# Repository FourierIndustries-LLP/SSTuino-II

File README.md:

Designed by FourierIndustries LLP | Designed and tested in Singapore

# SSTuino II

SSTuino II is an easy to use and industrial-ready Wi-Fi enabled microcontroller, designed and fabricated by SST Alumni. With a smaller form factor, improved Wi-Fi and processing capabilities, this is the next generation of SSTuino.

**SSTuino II documentation available at: https://knowledge.fourier.industries**

## Technical information

### Pinout diagram

### Repository Layout

* **SSTuino_II**: CAD files for SSTuino II
* **SSTuinoII_Jig**: CAD files for the SSTuino II test jig
* **Manufacturing**: Manufacturing files (Gerbers, BOM, component placement)
* **Documentation**: Documentation for design and manufacturing (not user manuals)
* **Tooling**: Software tools for production and debugging of the SSTuino II

### Automatic repair tool

Paste and run the following command in your terminal to run the autorepair tool, should you run into difficulty launching Arduino IDE or uploading programs onto your SSTuino II. Follow the on-screen instructions carefully. 

Note: This tool is only compatible with Arduino IDE 2. 

```shell
/bin/bash -c "$(curl -fsSL https://raw.githubusercontent.com/FourierIndustries-LLP/SSTuino-II/HEAD/Tooling/sstuino-autorepair.sh)"
```

## Contributing

Contributing to the SSTuino II Git Repository requires you to have EAGLE 8.4 or newer which supports Managed Libraries.

SSTuino II primarily uses EAGLE's Managed Libraries made by Sparkfun, but also contain our own custom footprints and SMD component footprints from various manufacturers.

SSTuino II is derived from the [Arduino Uno WiFi REV2](https://store-usa.arduino.cc/products/arduino-uno-wifi-rev2), and is licensed under a [CC BY-SA 4.0 International license](http://creativecommons.org/licenses/by-sa/4.0/).

## Our team

* Goh Qian Zhe ([@QianZheGoh](https://twitter.com/QianZheGoh))
* Pan Ziyue ([@d3lta-v](https://twitter.com/sammy0025))

And special acknowledgement to the awesome folks at Arduino, Sparkfun and Adafruit for technical reference and ECAD models.

Open Source Hardware (OSHW)

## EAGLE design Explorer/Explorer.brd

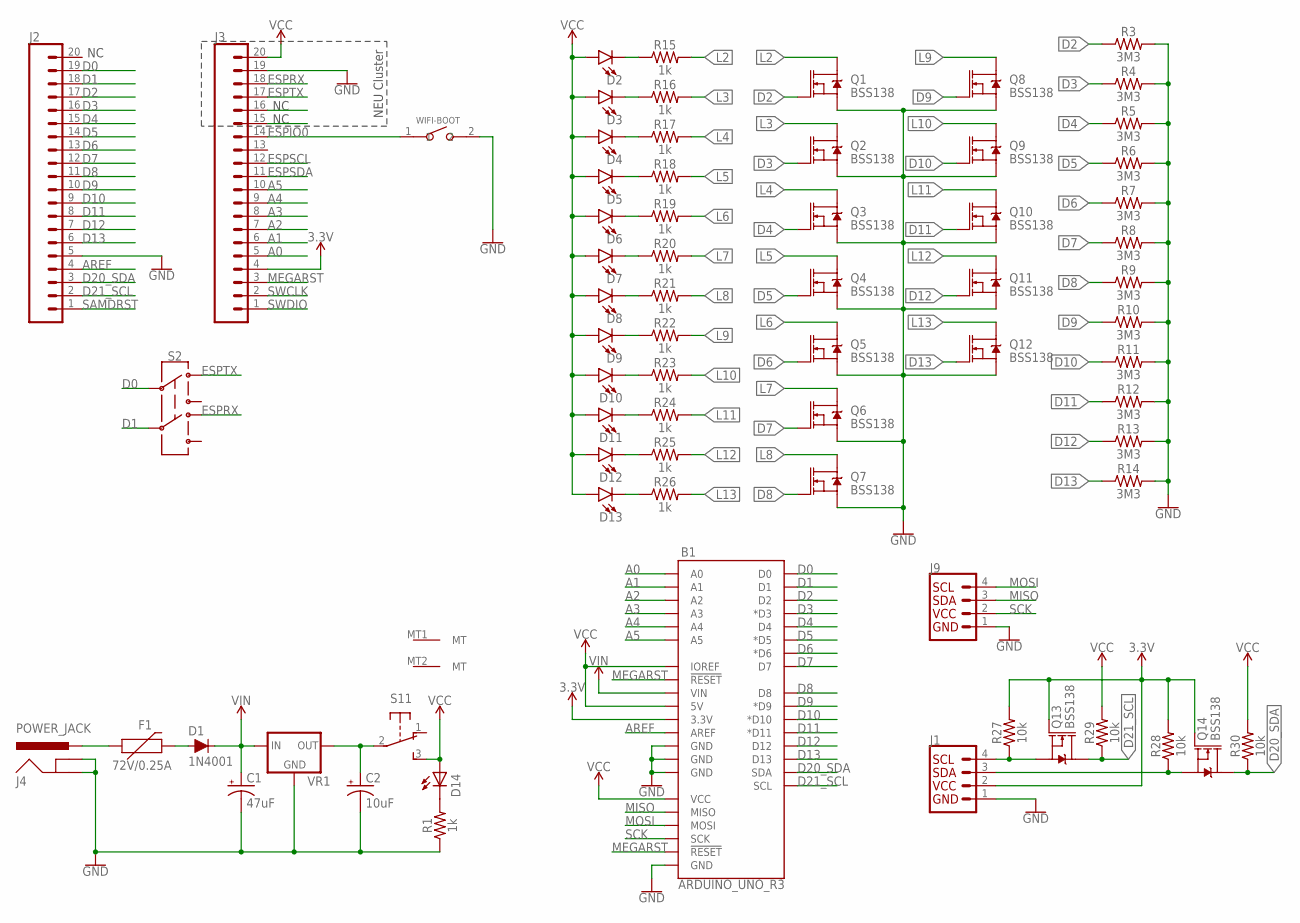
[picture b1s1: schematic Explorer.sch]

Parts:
B1: ARDUINO_UNO_R3; ARDUINO_R3
C1: 47uF; CPOL-RADIAL-2.5MM-6.5MM
C2: 10uF; CPOL-RADIAL-2.5MM-6.5MM
D1: 1N4001; DIODE-1N4001-KIT
D2, D3, D4, D5, D6, D7, D8, D9, D10, D11, D12, D13: LED0603; LED-0603; LCSC_PART C2286
D14: LEDCHIPLED_0805; CHIPLED_0805; LCSC_PART C2296
F1: 72V/0.25A; PTH
J1, J9: QWIIC_CONNECTORJS-1MM; 1X04_1MM_RA; LCSC_PART C239522
J2, J3: CONN_20; 1X20; LCSC_PART C50984
J4: POWER_JACK; POWER_JACK_PTH
Q1, Q2, Q3, Q4, Q5, Q6, Q7, Q8, Q9, Q10, Q11, Q12, Q13, Q14: BSS138; SOT23-3; LCSC_PART C435876
R1, R15, R16, R17, R18, R19, R20, R21, R22, R23, R24, R25, R26: 1k; 0603; LCSC_PART C21190
R3, R4, R5, R6, R7, R8, R9, R10, R11, R12, R13, R14: 3M3; 0603; LCSC_PART C103556
R27, R28, R29, R30: 10k; 0603; LCSC_PART C25804
S1: EG1213
S2: SWITCH-DPDT-SMD-AYZ0202; SWITCH_DPDT_SMD_AYZ0202; LCSC_PART C318999
VR1: V_REG_78XXSINK; TO220-IGO
WIFI-BOOT: SKRKAEE020; SW2-2.6-3.9X2.9X1.5+0.4MM; LCSC_PART C455280

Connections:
3.3V: B1.3.3V, J1.2 (VCC), J3.4, Q13.1 (G), Q14.1 (G), R27.2, R28.2
A0: B1.A0, J3.5
A1: B1.A1, J3.6
A2: B1.A2, J3.7
A3: B1.A3, J3.8
A4: B1.A4, J3.9
A5: B1.A5, J3.10
AREF: B1.AREF, J2.4
D0: B1.D0, J2.19, S2.2
D1: B1.D1, J2.18, S2.5
D2: B1.D2, J2.17, Q1.1 (G), R3.1
D3: B1.D3 (*D3), J2.16, Q2.1 (G), R4.1
D4: B1.D4, J2.15, Q3.1 (G), R5.1
D5: B1.D5 (*D5), J2.14, Q4.1 (G), R6.1
D6: B1.D6 (*D6), J2.13, Q5.1 (G), R7.1
D7: B1.D7, J2.12, Q6.1 (G), R8.1
D8: B1.D8, J2.11, Q7.1 (G), R9.1
D9: B1.D9 (*D9), J2.10, Q8.1 (G), R10.1
D10: B1.D10 (*D10), J2.9, Q9.1 (G), R11.1
D11: B1.D11 (*D11), J2.8, Q10.1 (G), R12.1
D12: B1.D12, J2.7, Q11.1 (G), R13.1
D13: B1.D13, J2.6, Q12.1 (G), R14.1
D20_SDA: B1.SDA, J2.3, Q14.3 (D), R30.1
D21_SCL: B1.SCL, J2.2, Q13.3 (D), R29.1
ESPIO0: J3.14, WIFI-BOOT.1
ESPRX: J3.18, S2.4
ESPSCL: J3.12
ESPSDA: J3.11
ESPTX: J3.17, S2.1
GND: B1.GND@1 (GND), B1.GND@2 (GND), B1.GND@3 (GND), B1.GND@4 (GND), C1.2 (-), C2.2 (-), J1.1 (GND), J2.5, J3.19, J4.GND, J4.GNDBREAK, J9.1 (GND), Q1.2 (S), Q2.2 (S), Q3.2 (S), Q4.2 (S), Q5.2 (S), Q6.2 (S), Q7.2 (S), Q8.2 (S), Q9.2 (S), Q10.2 (S), Q11.2 (S), Q12.2 (S), R1.1, R3.2, R4.2, R5.2, R6.2, R7.2, R8.2, R9.2, R10.2, R11.2, R12.2, R13.2, R14.2, VR1.GND, WIFI-BOOT.2
L2: Q1.3 (D), R15.2
L3: Q2.3 (D), R16.2
L4: Q3.3 (D), R17.2
L5: Q4.3 (D), R18.2
L6: Q5.3 (D), R19.2
L7: Q6.3 (D), R20.2
L8: Q7.3 (D), R21.2
L9: Q8.3 (D), R22.2
L10: Q9.3 (D), R23.2
L11: Q10.3 (D), R24.2
L12: Q11.3 (D), R25.2
L13: Q12.3 (D), R26.2
MEGARST: B1.RESET@1 (!RESET!), B1.RESET@2 (!RESET!), J3.3
MISO: B1.MISO, J9.3 (SDA)
MOSI: B1.MOSI, J9.4 (SCL)
unnamed: F1.P$1 (1), J4.PWR
unnamed: D1.A, F1.P$2 (2)
unnamed: D14.C, R1.2
unnamed: C2.1 (+), S1.2, VR1.OUT
unnamed: D13.C, R26.1
unnamed: D12.C, R25.1
unnamed: D11.C, R24.1
unnamed: D10.C, R23.1
unnamed: D9.C, R22.1
unnamed: D8.C, R21.1
unnamed: D7.C, R20.1
unnamed: D6.C, R19.1
unnamed: D5.C, R18.1
unnamed: D4.C, R17.1
unnamed: D3.C, R16.1
unnamed: D2.C, R15.1
SAMDRST: J2.1
SCK: B1.SCK, J9.2 (VCC)
SCL_3V: J1.4 (SCL), Q13.2 (S), R27.1
SDA_3V: J1.3 (SDA), Q14.2 (S), R28.1
SWCLK: J3.2
SWDIO: J3.1
VCC: B1.5V, B1.IOREF, B1.VCC, D2.A, D3.A, D4.A, D5.A, D6.A, D7.A, D8.A, D9.A, D10.A, D11.A, D12.A, D13.A, D14.A, J3.20, R29.2, R30.2, S1.3 (S)
VIN: B1.VIN, C1.1 (+), D1.C, VR1.IN

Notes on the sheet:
NEU Cluster

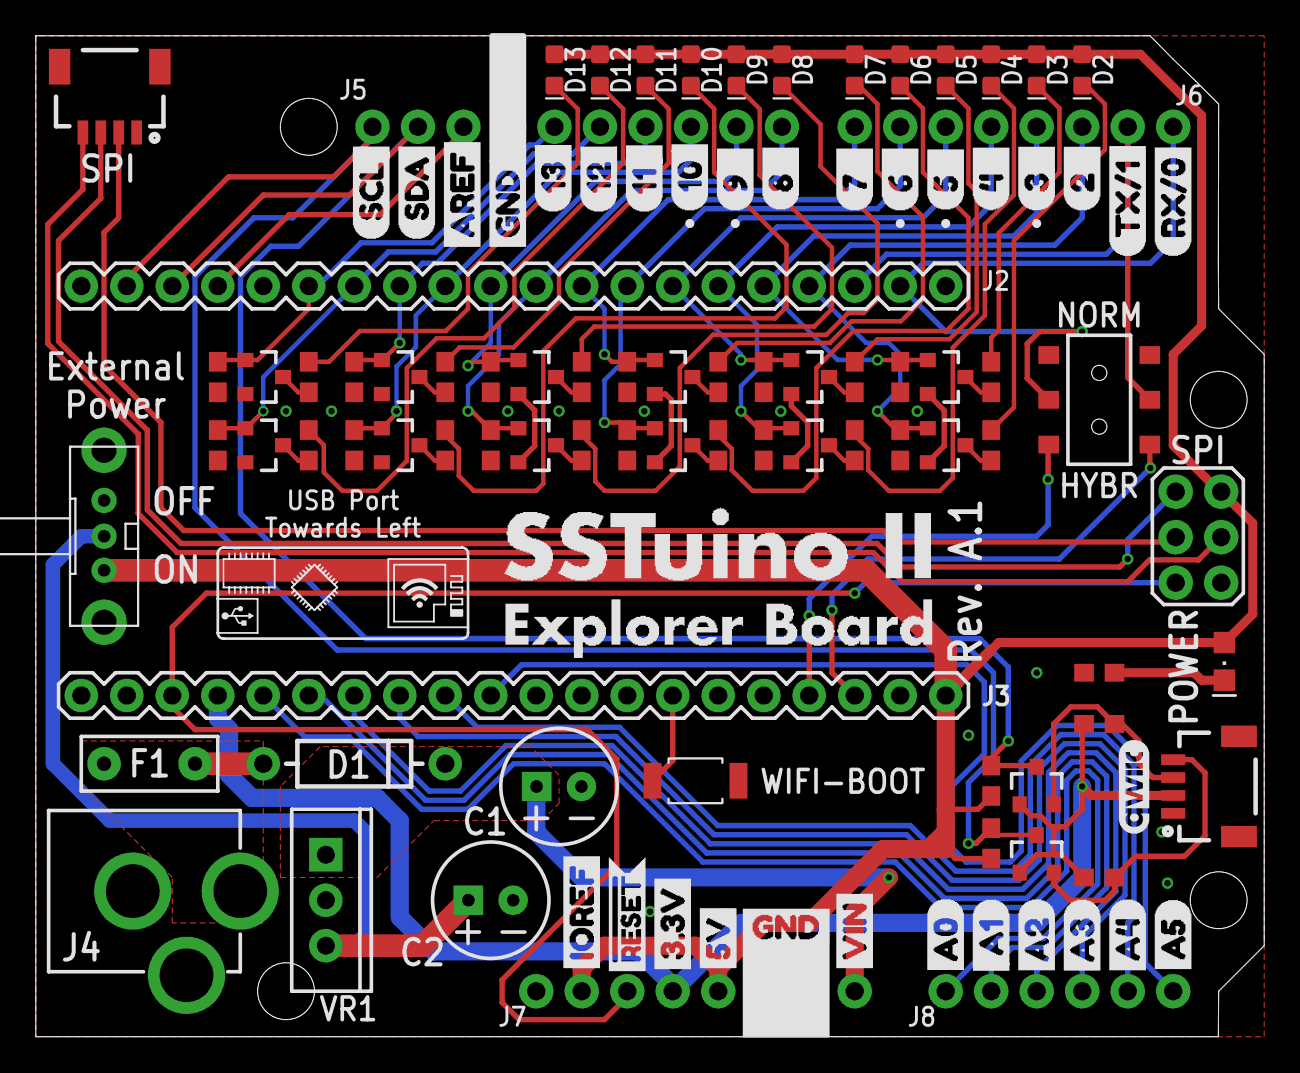
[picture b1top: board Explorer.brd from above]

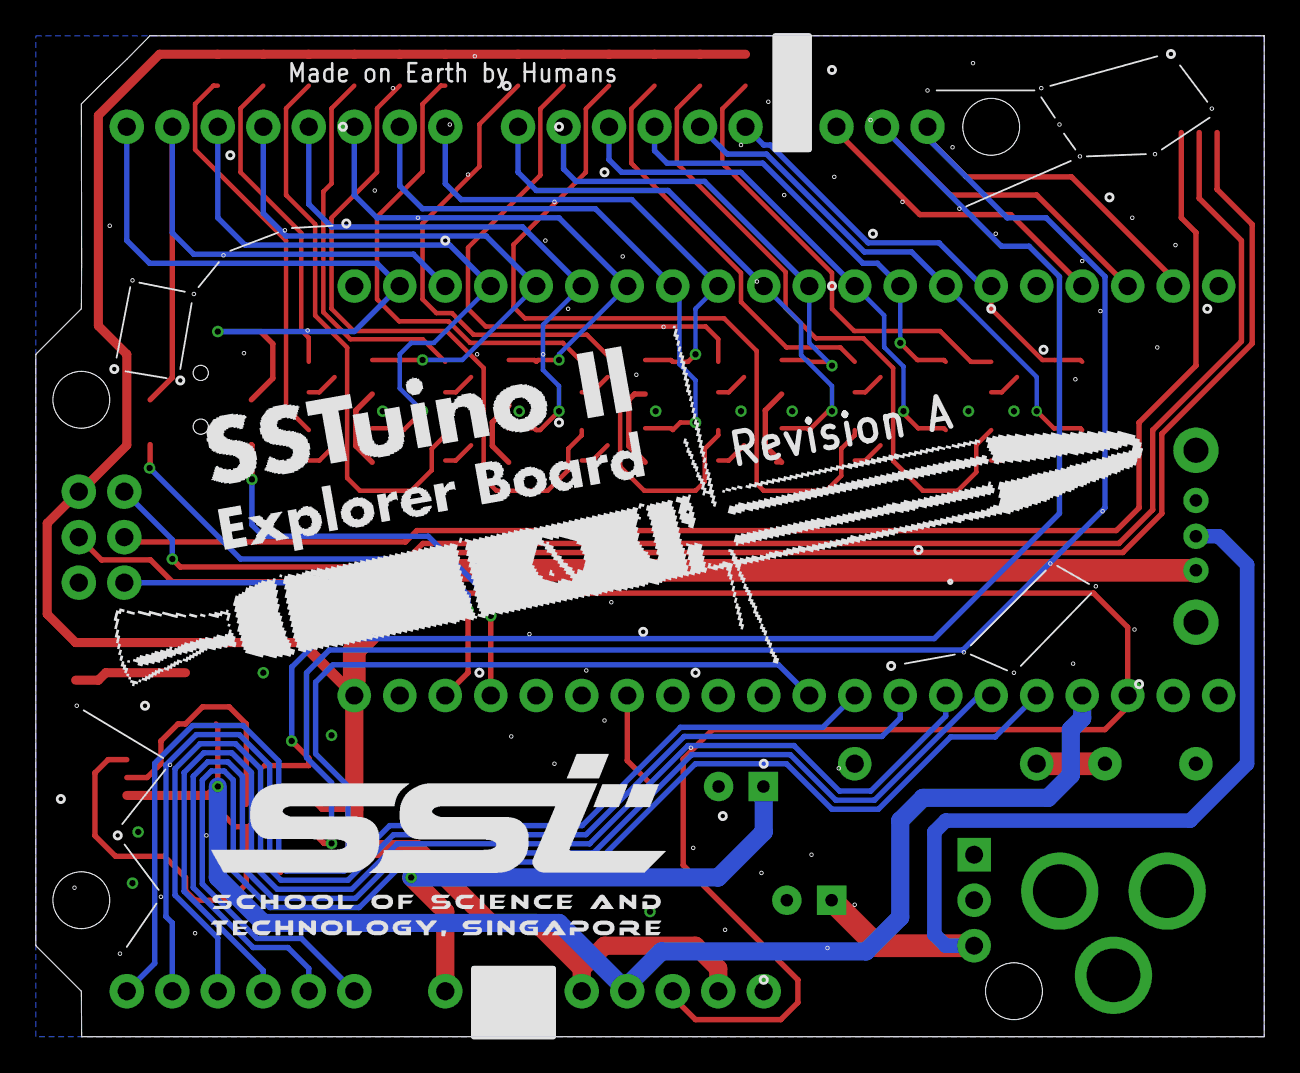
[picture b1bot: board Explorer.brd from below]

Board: 2 copper layers, 68.6 x 55.9 mm, 117 parts (13 on the bottom side), 64 nets.

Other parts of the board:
U$1: IOREF9
U$2: 3#3V7
U$3: #RESET28
U$4: 5V8
U$5, U$25: GND6
U$6: A00
U$7: A11
U$8: SST-BIG
U$9: EXPLORER
U$10: STARFIELD_URSAMINOR
U$11: STARFIELD_SMALL
U$12: STARFIELD_ORION
U$13: STARFIELD_LYRA
U$14: STARFIELD_CASSIOPEIA
U$15, U$16, U$17, U$18, U$19: STARFIELD_SMALL2
U$20: A22
U$21, U$45: EXPLORER_BOARD_LARGE
U$22: A33
U$23: A44
U$24: A55
U$26: 1314
U$27: 1215
U$28: 1116
U$29: 1017
U$30: 9__18
U$31: 8__19
U$32: 7__20
U$33: 6__21
U$34: 5__22
U$35: 4__23
U$36: 3__24
U$37: 2__25
U$38: TX#127
U$39: RX#026
U$40: AREF13
U$41: SDA25
U$42: SCL26
U$43: VIN10
U$44: QWIIC_LOGO
U$46: USBLOGO#PNG
U$47: WIFILOGO#JPG

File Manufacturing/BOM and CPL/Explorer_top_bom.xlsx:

Comment | Designator | Footprint | LCSC Part #
 | D2 D3 D4 D5 D6 D7 D8 D9 D10 D11 D12 D13 | LED-0603 | C2286
 | D14 | LED-0805 | C2296
 | J1 J9 | 1X04_1MM_JST_SH | C145956
 | J2 J3 | 1X20P_FEMALE | C50984
 | S2 | SWITCH_DPDT_SMD_AYZ0202 | C318999
1k | R1 R15 R16 R17 R18 R19 R20 R21 R22 R23 R24 R25 R26 | RES-0603 | C21190
3M3 | R3 R4 R5 R6 R7 R8 R9 R10 R11 R12 R13 R14 | RES-0603 | C39227
10k | R27 R28 R29 R30 | RES-0603 | C25804
BSS138 | Q1 Q2 Q3 Q4 Q5 Q6 Q7 Q8 Q9 Q10 Q11 Q12 Q13 Q14 | SOT23-3 | C435876
SKRKAEE020 | WIFI-BOOT WIFI-RESET | SW2-2.6-3.9X2.9X1.5+0.4MM | C455280
 | J5 | 1X10P_FEMALE | C35445
 | J6 J7 | 1X8P_FEMALE | C27438
 | J8 | 1X6P_FEMALE | C40877
0 | R2 R31 | RES-0603 | C21189

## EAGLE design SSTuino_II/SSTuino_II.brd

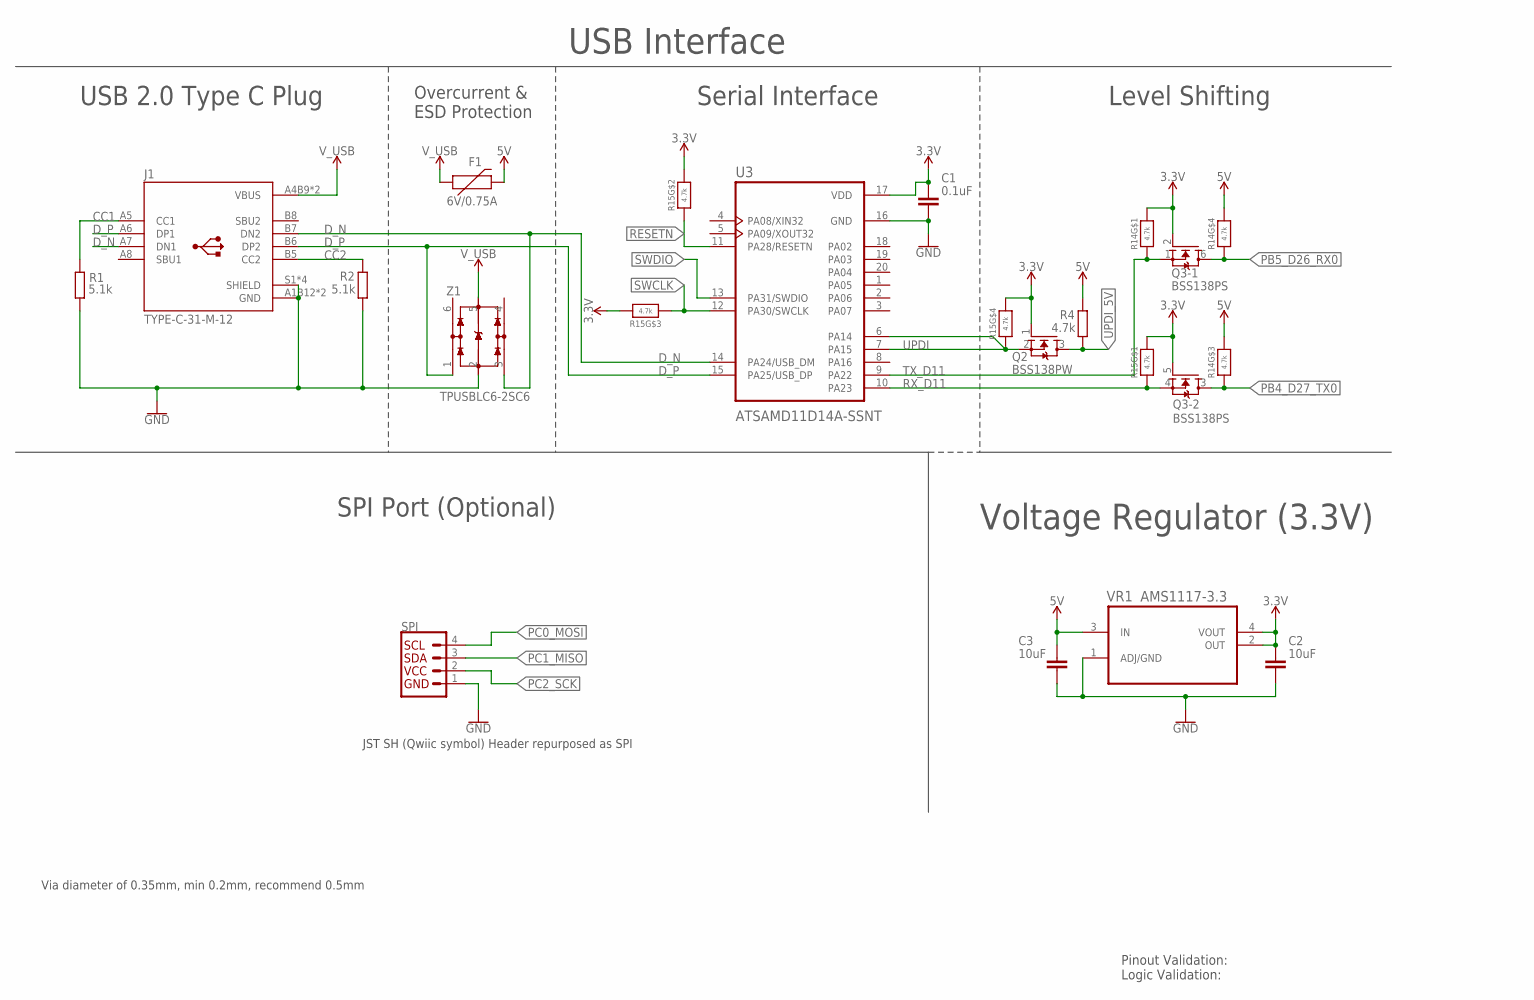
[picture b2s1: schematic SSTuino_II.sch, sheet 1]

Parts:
C1: 0.1uF; CAPC1005X60; LCSC_PART C696352
C2, C3: 10uF; CAPC1608X85; LCSC_PART C19702
F1: 6V/0.75A; 1206; LCSC_PART C99563
J1: TYPE-C-31-M-12; HRO_TYPE-C-31-M-12; LCSC_PART C165948
Q2: BSS138PW; SOT65P210X110-3N; LCSC_PART C193366
Q3: BSS138PS; ARDUINO-TRANSISTORS_SOT363; LCSC_PART C193381
R1, R2: 5.1k; RESC1005X40; LCSC_PART C25905
R4: 4.7k; RESC1005X40; LCSC_PART C25900
R14, R15: 4.7k; RESPACK_4X0402; LCSC_PART C29586
SPI: QWIIC_CONNECTORJS-1MM; 1X04_1MM_RA
U3: ATSAMD11D14A-SSNT; SOIC127P1030X265-20N; LCSC_PART C2053599
VR1: AMS1117-3.3; SOT230P696X180-4N; LCSC_PART C6186
Z1: TPUSBLC6-2SC6; SOT95P280X110-6N; LCSC_PART C558442

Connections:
3.3V: C1.1, C2.1, Q2.1 (G), Q3.2 (G), Q3.5 (G), R14.8 (2), R15.5 (2), R15.6 (2), R15.7 (2), R15.8 (2), U3.17 (VDD), VR1.2 (OUT), VR1.4 (VOUT); also elsewhere on the board
5V: C3.1, F1.2, R4.2, R14.5 (2), R14.6 (2), VR1.3 (IN); also elsewhere on the board
CC1: J1.A5 (CC1), R1.1
CC2: J1.B5 (CC2), R2.2
D_N: J1.A7 (DN1), J1.B7 (DN2), U3.14 (PA24/USB_DM), Z1.3 (IO2)
D_P: J1.A6 (DP1), J1.B6 (DP2), U3.15 (PA25/USB_DP), Z1.1 (IO1)
GND: C1.2, C2.2, C3.2, J1.A1B12 (GND), J1.B1A12 (GND), J1.S1 (SHIELD), J1.S2 (SHIELD), J1.S3 (SHIELD), J1.S4 (SHIELD), R1.2, R2.1, SPI.1 (GND), U3.16 (GND), VR1.1 (ADJ/GND), Z1.2 (VSS); also elsewhere on the board
PB4_D27_TX0: Q3.3 (D), R14.3 (1); also elsewhere on the board
PB5_D26_RX0: Q3.6 (D), R14.4 (1); also elsewhere on the board
PC0_MOSI: SPI.4 (SCL); also elsewhere on the board
PC1_MISO: SPI.3 (SDA); also elsewhere on the board
PC2_SCK: SPI.2 (VCC); also elsewhere on the board
RESETN: R15.2 (1), U3.11 (PA28/RESETN); also elsewhere on the board
RX_D11: Q3.4 (S), R15.1, U3.10 (PA23)
SWCLK: R15.3 (1), U3.12 (PA30/SWCLK); also elsewhere on the board
SWDIO: U3.13 (PA31/SWDIO); also elsewhere on the board
TX_D11: Q3.1 (S), R14.1, U3.9 (PA22)
UPDI: Q2.2 (S), R15.4 (1), U3.6 (PA14), U3.7 (PA15)
UPDI_5V: Q2.3 (D), R4.1; also elsewhere on the board
V_USB: F1.1, J1.A4B9 (VBUS), J1.B4A9 (VBUS), Z1.5 (VCC)

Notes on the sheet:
Via diameter of 0.35mm, min 0.2mm, recommend 0.5mm
USB Interface
Voltage Regulator (3.3V)
USB 2.0 Type C Plug
Overcurrent & ESD Protection
Serial Interface
Level Shifting
Pinout Validation: Logic Validation:
JST SH (Qwiic symbol) Header repurposed as SPI
SPI Port (Optional)

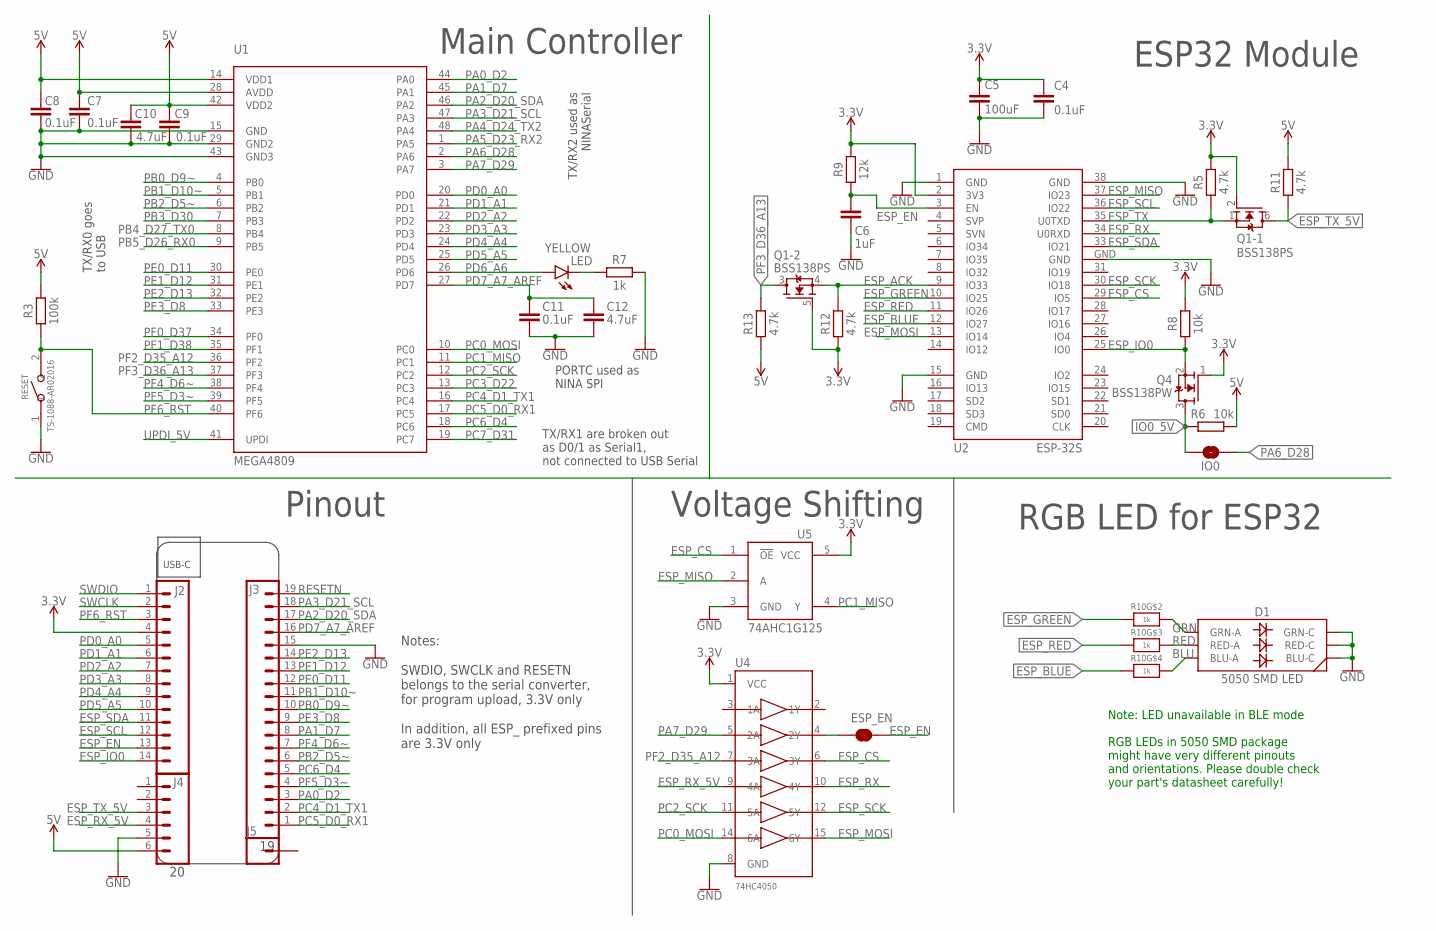
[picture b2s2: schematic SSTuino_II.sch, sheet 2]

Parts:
C4, C11: 0.1uF; CAPC1005X60; LCSC_PART C1525
C5: 100uF; CAPC3216X135; LCSC_PART C15008
C6: 1uF; CAPC1005X60; LCSC_PART C52923
C7, C8, C9: 0.1uF; CAPC1005X60
C10: 4.7uF; CAPC1005X60
C12: 4.7uF; CAPC1005X60; LCSC_PART C23733
D1: 5050 SMD LED; LED-TRICOLOR-5050; LCSC_PART C784540
ESP_EN: JUMPER-SMT_2_NC_TRACE_SILK; SMT-JUMPER_2_NC_TRACE_SILK
IO0: JUMPER-SMT_2_NO_SILK; SMT-JUMPER_2_NO_SILK
J2: CONN_14NO_SILK; 1X14_NO_SILK
J3: CONN_191X19_NO_SILK; 1X19_NO_SILK
J4: CONN_06NO_SILK_FEMALE_PTH; 1X06_NO_SILK
J5: CONN_01PTH_NO_SILK_YES_STOP; 1X01_NO_SILK
LED: YELLOW; LED-0603; LCSC_PART C72038
Q1: BSS138PS; ARDUINO-TRANSISTORS_SOT363; LCSC_PART C193381
Q4: BSS138PW; SOT65P210X110-3N; LCSC_PART C919583
R3: 100k; RESC1005X40; LCSC_PART C25741
R5, R11, R12, R13: 4.7k; RESC1005X40; LCSC_PART C25900
R6, R8: 10k; RESC1005X40; LCSC_PART C25744
R7: 1k; RESC1005X40; LCSC_PART C11702
R9: 12k; RESC1005X40; LCSC_PART C25752
R10: 1k; RESPACK_4X0402; LCSC_PART C25726
RESET: TS-1088-AR02016; SW2-2.6-3.9X2.9X1.5+0.4MM; LCSC_PART C720477
U1: MEGA4809; TQFP48; LCSC_PART C189475
U2: ESP-32S; LCSC_PART C277944
U4: 74HC4050; TSSOP16; LCSC_PART C352825
U5: 74AHC1G125; SOT23-5L; LCSC_PART C7468

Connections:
3.3V: C4.1, C5.1, J2.4, Q1.2 (G), Q1.5 (G), Q4.1 (G), R5.2, R8.2, R9.2, R12.1, U2.2 (3V3), U4.1 (VCC), U5.5 (VCC); also elsewhere on the board
5V: C7.1, C8.1, C9.1, C10.1, J4.6, R3.2, R6.1, R11.2, R13.1, U1.14 (VDD1), U1.28 (AVDD), U1.42 (VDD2); also elsewhere on the board
BLU: D1.6 (BLU-A), R10.5 (2)
ESP_ACK: Q1.4 (S), R12.2, U2.9 (IO33)
ESP_BLUE: R10.4 (1), U2.12 (IO27)
ESP_CS: U2.29 (IO5), U4.6 (3Y), U5.1 (!OE)
ESP_EN: C6.2, ESP_EN.2, J2.13, R9.1, U2.3 (EN)
ESP_EN_PRE: ESP_EN.1, U4.4 (2Y)
ESP_GREEN: R10.2 (1), U2.10 (IO25)
ESP_IO0: J2.14, Q4.2 (S), R8.1, U2.25 (IO0)
ESP_MISO: U2.37 (IO23), U5.2 (A)
ESP_MOSI: U2.13 (IO14), U4.15 (6Y)
ESP_RED: R10.3 (1), U2.11 (IO26)
ESP_RX: U2.34 (U0RXD), U4.10 (4Y)
ESP_RX_5V: J4.4, U4.9 (4A)
ESP_SCK: U2.30 (IO18), U4.12 (5Y)
ESP_SCL: J2.12, U2.36 (IO22)
ESP_SDA: J2.11, U2.33 (IO21)
ESP_TX: Q1.1 (S), R5.1, U2.35 (U0TXD)
ESP_TX_5V: J4.3, Q1.6 (D), R11.1
GND: C4.2, C5.2, C6.1, C7.2, C8.2, C9.2, C10.2, C11.2, C12.2, D1.1 (BLU-C), D1.2 (RED-C), D1.3 (GRN-C), J3.15, J4.5, R7.2, RESET.1, U1.15 (GND), U1.29 (GND2), U1.43 (GND3), U2.1 (GND), U2.15 (GND), U2.38 (GND), U2.GND, U4.8 (GND), U5.3 (GND); also elsewhere on the board
GRN: D1.4 (GRN-A), R10.7 (2)
IO0_5V: IO0.2, Q4.3 (D), R6.2
unnamed: LED.C, R7.1
PA0_D2: J3.3, U1.44 (PA0)
PA1_D7: J3.8, U1.45 (PA1)
PA2_D20_SDA: J3.17, U1.46 (PA2)
PA3_D21_SCL: J3.18, U1.47 (PA3)
PA4_D24_TX2: U1.48 (PA4)
PA5_D23_RX2: U1.1 (PA5)
PA6_D28: IO0.1, U1.2 (PA6)
PA7_D29: U1.3 (PA7), U4.5 (2A)
PB0_D9~: J3.10, U1.4 (PB0)
PB1_D10~: J3.11, U1.5 (PB1)
PB2_D5~: J3.6, U1.6 (PB2)
PB3_D30: U1.7 (PB3)
PB4_D27_TX0: U1.8 (PB4); also elsewhere on the board
PB5_D26_RX0: U1.9 (PB5); also elsewhere on the board
PC0_MOSI: U1.10 (PC0), U4.14 (6A); also elsewhere on the board
PC1_MISO: U1.11 (PC1), U5.4 (Y); also elsewhere on the board
PC2_SCK: U1.12 (PC2), U4.11 (5A); also elsewhere on the board
PC3_D22: U1.13 (PC3)
PC4_D1_TX1: J3.2, U1.16 (PC4)
PC5_D0_RX1: J3.1, U1.17 (PC5)
PC6_D4: J3.5, U1.18 (PC6)
PC7_D31: U1.19 (PC7)
PD0_A0: J2.5, U1.20 (PD0)
PD1_A1: J2.6, U1.21 (PD1)
PD2_A2: J2.7, U1.22 (PD2)
PD3_A3: J2.8, U1.23 (PD3)
PD4_A4: J2.9, U1.24 (PD4)
PD5_A5: J2.10, U1.25 (PD5)
PD6_A6: LED.A, U1.26 (PD6)
PD7_A7_AREF: C11.1, C12.1, J3.16, U1.27 (PD7)
PE0_D11: J3.12, U1.30 (PE0)
PE1_D12: J3.13, U1.31 (PE1)
PE2_D13: J3.14, U1.32 (PE2)
PE3_D8: J3.9, U1.33 (PE3)
PF0_D37: U1.34 (PF0)
PF1_D38: U1.35 (PF1)
PF2_D35_A12: U1.36 (PF2), U4.7 (3A)
PF3_D36_A13: Q1.3 (D), R13.2, U1.37 (PF3)
PF4_D6~: J3.7, U1.38 (PF4)
PF5_D3~: J3.4, U1.39 (PF5)
PF6_RST: J2.3, R3.1, RESET.2, U1.40 (PF6)
RED: D1.5 (RED-A), R10.6 (2)
RESETN: J3.19; also elsewhere on the board
SWCLK: J2.2; also elsewhere on the board
SWDIO: J2.1; also elsewhere on the board
UPDI_5V: U1.41 (UPDI); also elsewhere on the board

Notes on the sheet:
TX/RX2 used as NINASerial
PORTC used as NINA SPI
TX/RX1 are broken out as D0/1 as Serial1, not connected to USB Serial
TX/RX0 goes to USB
Note: LED unavailable in BLE mode RGB LEDs in 5050 SMD package might have very different pinouts and orientations. Please double check your part's datasheet carefully!
USB-C
ESP32 Module
Main Controller
Pinout
Voltage Shifting
RGB LED for ESP32
Notes: SWDIO, SWCLK and RESETN belongs to the serial converter, for program upload, 3.3V only In addition, all ESP_ prefixed pins are 3.3V only

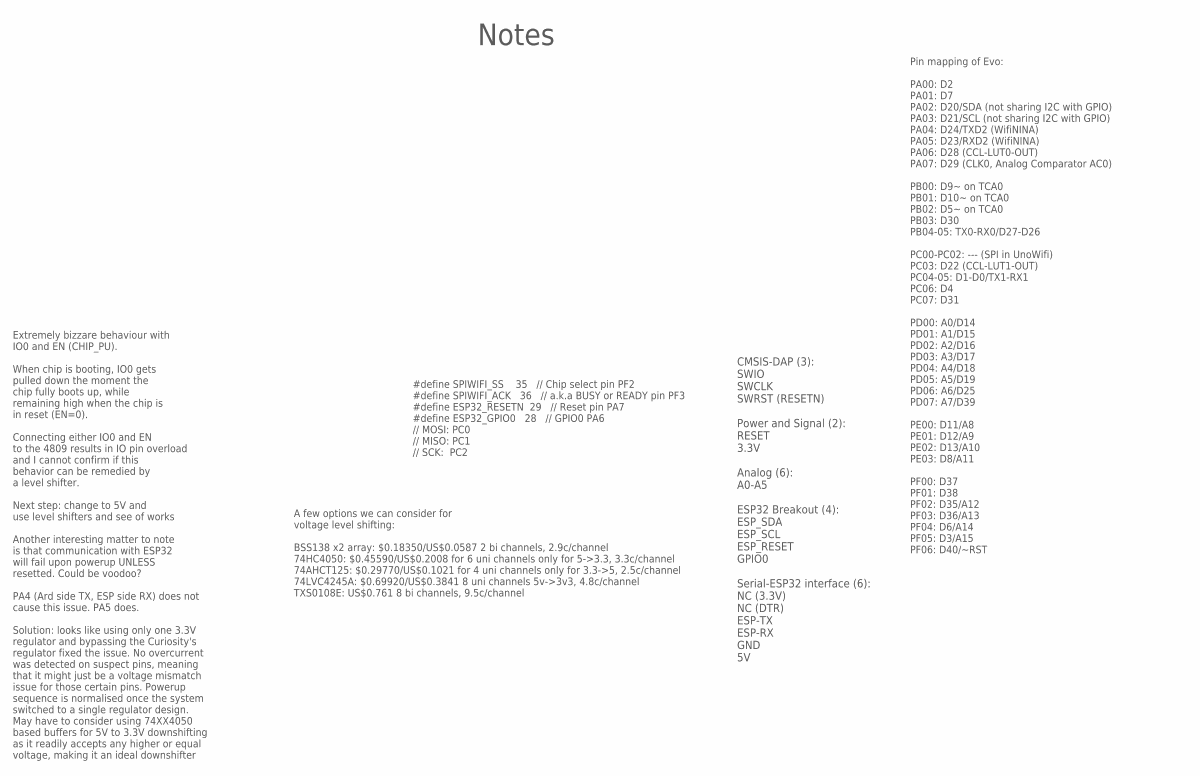
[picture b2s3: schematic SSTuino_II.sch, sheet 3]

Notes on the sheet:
Extremely bizzare behaviour with IO0 and EN (CHIP_PU). When chip is booting, IO0 gets pulled down the moment the chip fully boots up, while remaining high when the chip is in reset (EN=0). Connecting either IO0 and EN to the 4809 results in IO pin overload and I cannot confirm if this behavior can 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
#define SPIWIFI_SS 35 // Chip select pin PF2 #define SPIWIFI_ACK 36 // a.k.a BUSY or READY pin PF3 #define ESP32_RESETN 29 // Reset pin PA7 #define ESP32_GPIO0 28 // GPIO0 PA6 // MOSI: PC0 // MISO: PC1 // SCK: PC2
Pin mapping of Evo: PA00: D2 PA01: D7 PA02: D20/SDA (not sharing I2C with GPIO) PA03: D21/SCL (not sharing I2C with GPIO) PA04: D24/TXD2 (WifiNINA) PA05: D23/RXD2 (WifiNINA) PA06: D28 (CCL-LUT0-OUT) PA07: D29 (CLK0, Analog Comparator AC0) PB00: D9~ on TCA0 PB01: D10~ on TCA0 PB02: D5~ on TCA0 PB03: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
A few options we can consider for voltage level shifting: BSS138 x2 array: $0.18350/US$0.0587 2 bi channels, 2.9c/channel 74HC4050: $0.45590/US$0.2008 for 6 uni channels only for 5->3.3, 3.3c/channel 74AHCT125: $0.29770/US$0.1021 for 4 uni channels only for 3.3->5, 2.5c/channel 74LVC4245A: $0.69920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
Notes
CMSIS-DAP (3): SWIO SWCLK SWRST (RESETN) Power and Signal (2): RESET 3.3V Analog (6): A0-A5 ESP32 Breakout (4): ESP_SDA ESP_SCL ESP_RESET GPIO0 Serial-ESP32 interface (6): NC (3.3V) NC (DTR) ESP-TX ESP-RX GND 5V

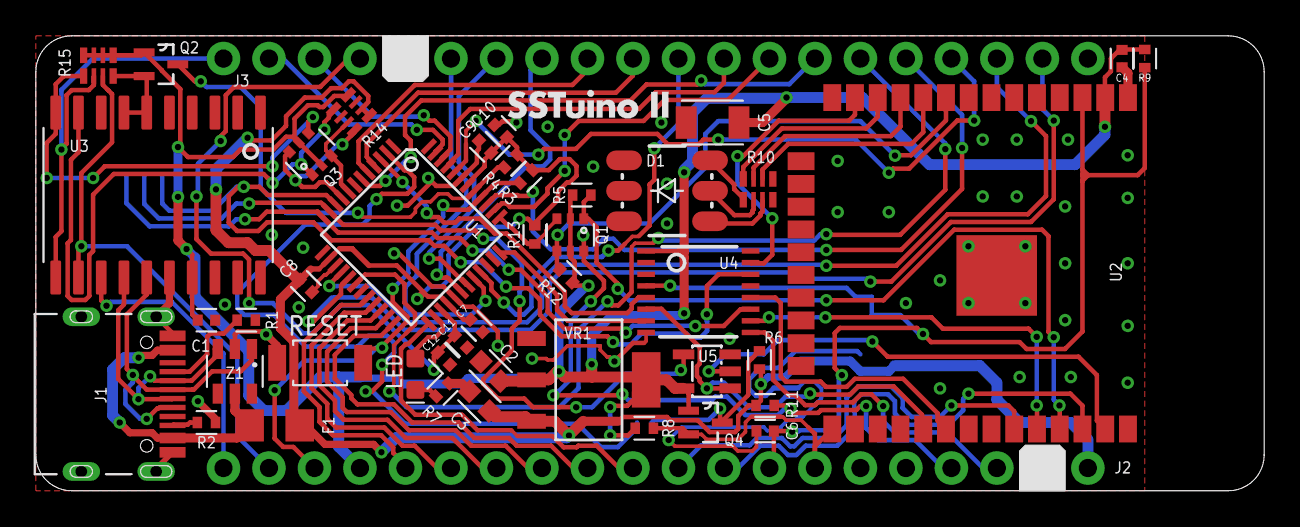
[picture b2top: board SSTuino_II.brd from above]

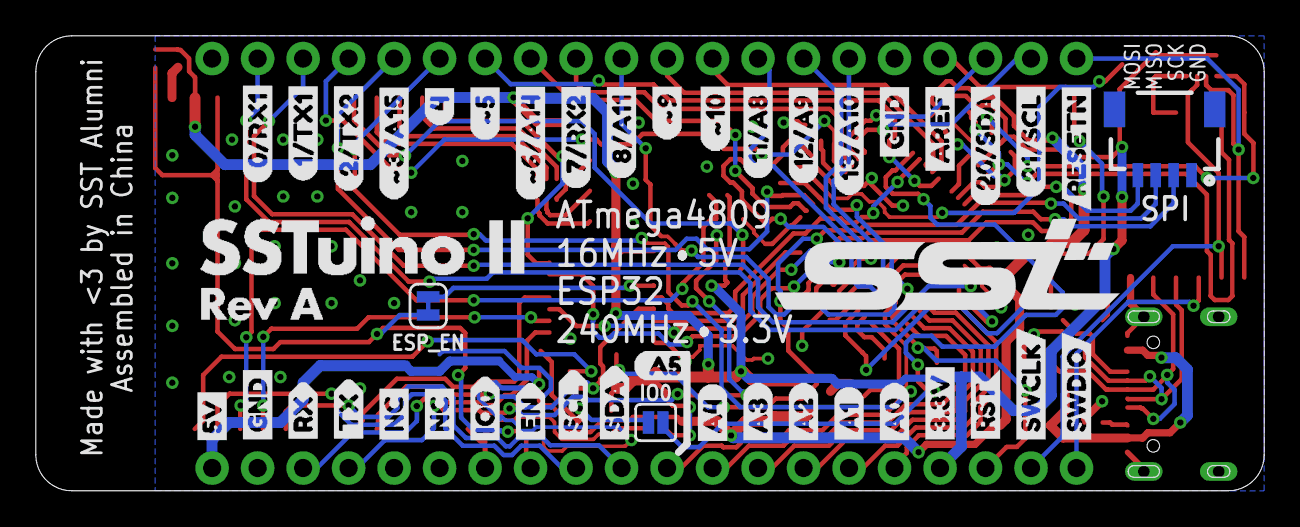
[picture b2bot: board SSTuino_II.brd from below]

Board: 2 copper layers, 68.6 x 25.4 mm, 92 parts (44 on the bottom side), 71 nets.

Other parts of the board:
U$1, U$2: LABEL-GND0
U$3, U$4: LABEL-NC0
U$5: LABEL-#3#A159
U$6: SSTUINOII-REVA-FUTURA-1LINE
U$7: LABEL-#6#A1412
U$8: LABEL-#511
U$9: LABEL-#916
U$10: LABEL-#1017
U$11: LABEL-0#RX17
U$12: LABEL-1#TX18
U$13: LABEL-2#TX214
U$14: LABEL-3#3V6
U$15: LABEL-7#RX213
U$16: LABEL-8#A1115
U$17: LABEL-11#A818
U$18: LABEL-12#A919
U$19: LABEL-13#A1020
U$20: LABEL-20#SDA2
U$21: LABEL-21#SCL3
U$22: LABEL-410
U$23: LABEL-AREF4
U$24: LABEL-SWCLK1
U$25: LABEL-SWDIO0
U$26: LABEL-5V5
U$27: LABEL-A01
U$28: LABEL-IO03
U$29: LABEL-A23
U$30: LABEL-A34
U$31: LABEL-A45
U$32: LABEL-A56
U$33: LABEL-EN4
U$34: LABEL-RST0
U$35: LABEL-TX8
U$36: LABEL-RX7
U$37: LABEL-SCL5
U$38: LABEL-SDA6
U$39: LABEL-RESETN9
U$40: LABEL-A10
U$41: SSTUINOII-REVA-FUTURA-2
U$42: SST-LOGO-SVG

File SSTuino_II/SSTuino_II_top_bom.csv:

Comment,Designator,Footprint,LCSC Part #
0.1uF,C1 C4 C7 C8 C9 C11,CAPC1005X60,C1525
1k,R7,RESC1005X40,C11702
1k,R10,RESPACK_4X0402,C25726
1uF,C6,CAPC1005X60,C52923
4.7k,R4 R5 R11 R12 R13,RESC1005X40,C25900
4.7k,R14 R15,RESPACK_4X0402,C29586
4.7uF,C10 C12,CAPC1005X60,C23733
5.1k,R1 R2,RESC1005X40,C25905
6V/0.75A,F1,1206,C99563
10k,R6 R8,RESC1005X40,C25744
10uF,C2 C3,CAPC1608X85,C19702
12k,R9,RESC1005X40,C25752
74AHC1G125,U5,SOT23-5L,C7468
74HC4050,U4,TSSOP16,C352825
100k,R3,RESC1005X40,C25741
100uF,C5,CAPC3216X135,C15008
5050 SMD LED,D1,LED-TRICOLOR-5050,C784540
AMS1117-3.3,VR1,SOT230P696X180-4N,C6186
ATSAMD11D14A-SSNT,U3,SOIC127P1030X265-20N,C2053599
BSS138PS,Q1 Q3,ARDUINO-TRANSISTORS_SOT363,C193381
BSS138PW,Q2 Q4,SOT65P210X110-3N,C919583
ESP-32S,U2,ESP-32S,C277944
MEGA4809,U1,TQFP48,C189475
TPUSBLC6-2SC6,Z1,SOT95P280X110-6N,C558442
TS-1088-AR02016,RESET,SW2-2.6-3.9X2.9X1.5+0.4MM,C720477
TYPE-C-31-M-12,J1,HRO_TYPE-C-31-M-12,C165948
YELLOW,LED,LED-0603,C72038

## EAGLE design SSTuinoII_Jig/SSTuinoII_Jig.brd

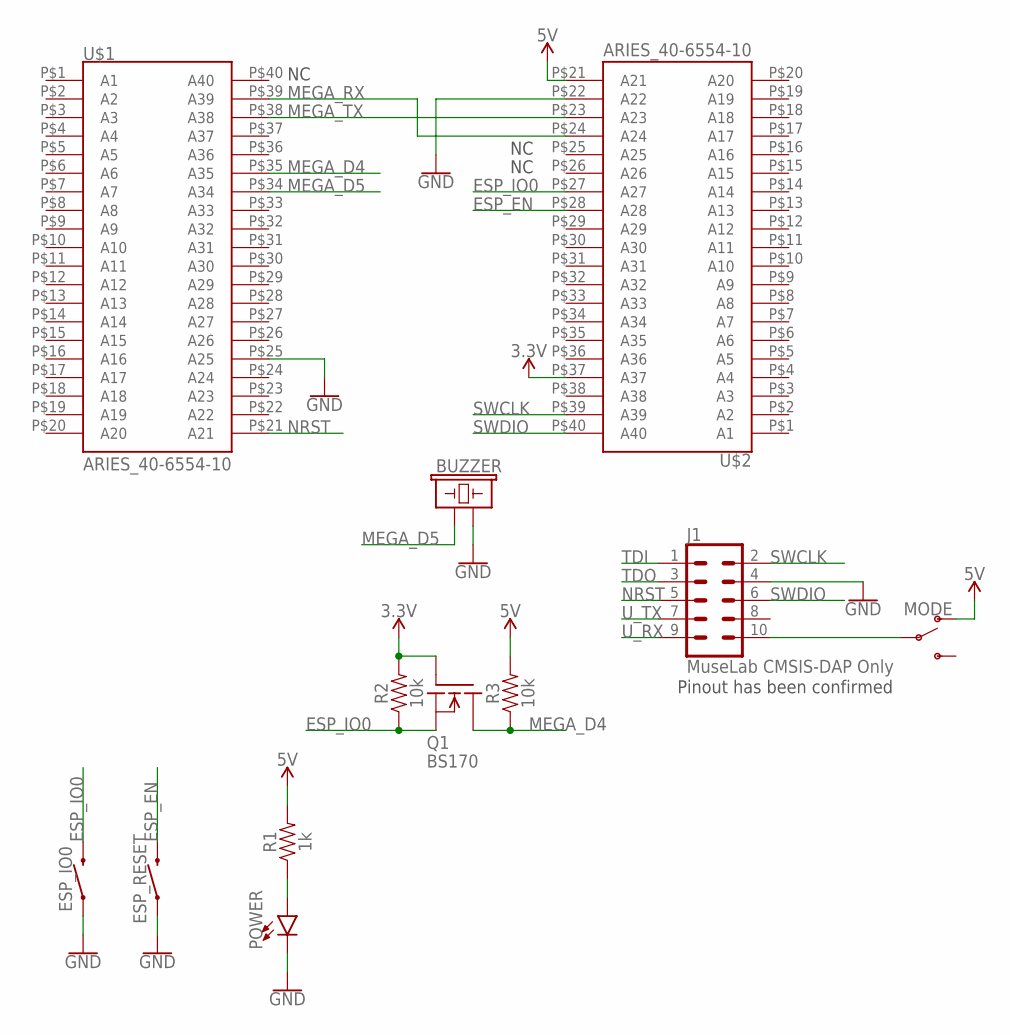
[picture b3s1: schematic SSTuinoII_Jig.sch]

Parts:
BUZZER: BUZZER-PTH_KIT; BUZZER-12MM-KIT
ESP_IO0: MOMENTARY-SWITCH-SPST-PTH-6.0MM-KIT; TACTILE_SWITCH_PTH_6.0MM_KIT
ESP_RESET: MOMENTARY-SWITCH-SPST-PTH-6.0MM-KIT; TACTILE_SWITCH_PTH_6.0MM_KIT
J1: MuseLab CMSIS-DAP Only; 2X5-SHROUDED_LOCK
MODE: SWITCH-SPDT-PTH-11.6X4.0MM-KIT; SWITCH_SPDT_PTH_11.6X4.0MM_KIT
POWER: LED3MM; LED_3MM
Q1: BS170; TO92
R1: 1k; AXIAL-0.3-KIT
R2, R3: 10k; AXIAL-0.3-KIT
U$1, U$2: ARIES_40-6554-10

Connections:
3.3V: Q1.2 (G), R2.P$2 (2), U$2.P$37 (A37)
5V: MODE.1 (O), R1.P$2 (2), R3.P$2 (2), U$2.P$21 (A21)
ESP_EN: ESP_RESET.3 (2), U$2.P$28 (A28)
ESP_IO0: ESP_IO0.3 (2), Q1.1 (S), R2.P$1 (1), U$2.P$27 (A27)
GND: BUZZER.- (2), ESP_IO0.1, ESP_RESET.1, J1.4, POWER.K (C), U$1.P$25 (A25), U$2.P$22 (A22)
MEGA_D4: Q1.3 (D), R3.P$1 (1), U$1.P$35 (A35)
MEGA_D5: BUZZER.+ (1), U$1.P$34 (A34)
MEGA_RX: U$1.P$39 (A39), U$2.P$24 (A24)
MEGA_TX: U$1.P$38 (A38), U$2.P$23 (A23)
unnamed: POWER.A, R1.P$1 (1)
NRST: J1.5, U$1.P$21 (A21)
PWR: J1.10, MODE.2
SWCLK: J1.2, U$2.P$39 (A39)
SWDIO: J1.6, U$2.P$40 (A40)
TDI: J1.1
TDO: J1.3
U_RX: J1.9
U_TX: J1.7

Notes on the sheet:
Pinout has been confirmed

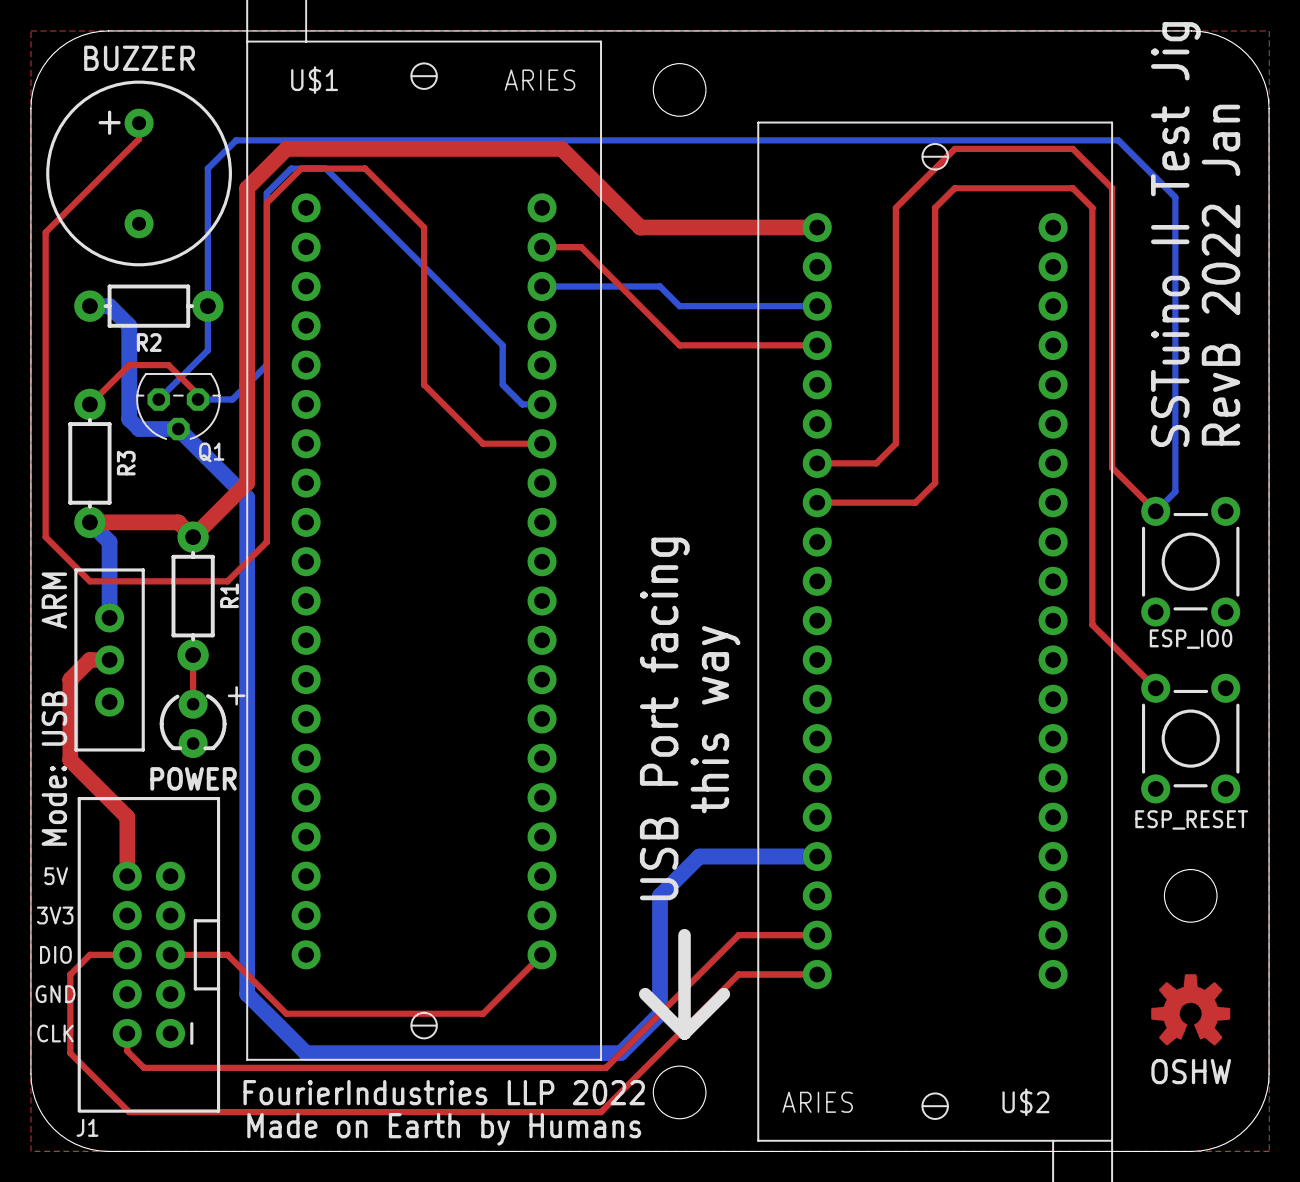
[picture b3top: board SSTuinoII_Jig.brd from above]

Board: 2 copper layers, 80.0 x 72.4 mm, 13 parts (0 on the bottom side), 14 nets.

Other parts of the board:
U$3: OSHW-LOGO-M_COPPER-SOLDERMASK

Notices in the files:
parts and their libraries:
SparkFun-Connectors: Licensing: Creative Commons ShareAlike 4.0 International - https://creativecommons.org/licenses/by-sa/4.0
esp32: Creative Commons Attribution-ShareAlike 4.0 International
